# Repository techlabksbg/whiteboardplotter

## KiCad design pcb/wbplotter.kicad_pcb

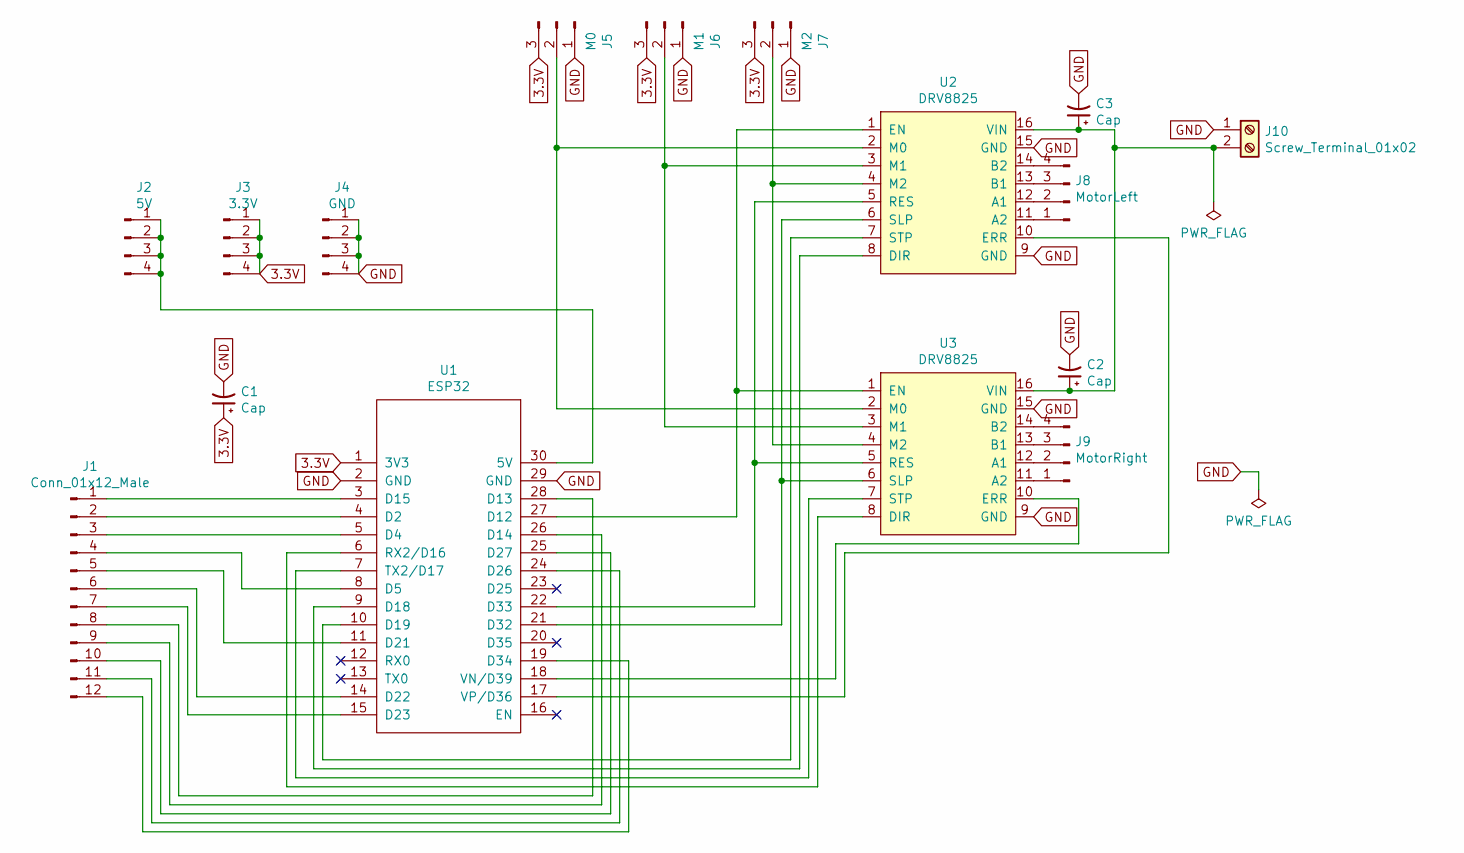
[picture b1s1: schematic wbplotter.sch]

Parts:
C1, C2, C3: Cap; CP_Radial_D6.3mm_P2.50mm
J1: Conn_01x12_Male; PinSocket_1x12_P2.54mm_Vertical
J2: 5V; PinSocket_1x04_P2.54mm_Vertical
J3: 3.3V; PinSocket_1x04_P2.54mm_Vertical
J4: GND; PinSocket_1x04_P2.54mm_Vertical
J5: M0; PinSocket_1x03_P2.54mm_Vertical
J6: M1; PinSocket_1x03_P2.54mm_Vertical
J7: M2; PinSocket_1x03_P2.54mm_Vertical
J8: MotorLeft; PinSocket_1x04_P2.54mm_Vertical
J9: MotorRight; PinSocket_1x04_P2.54mm_Vertical
J10: Screw_Terminal_01x02; TerminalBlock_Altech_AK300-2_P5.00mm
U1: ESP32; ESP32-Dev-Board
U2, U3: DRV8825

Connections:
3.3V: C1.1, J3.1, J3.2, J3.3, J3.4, J5.3, J6.3, J7.3, U1.1 (3V3)
GND: C1.2, C2.2, C3.2, J4.1, J4.2, J4.3, J4.4, J5.1, J6.1, J7.1, J10.1, U1.2 (GND), U1.29 (GND), U2.9 (GND), U2.15 (GND), U3.9 (GND), U3.15 (GND)
unnamed: C2.1, C3.1, J10.2, U2.16 (VIN), U3.16 (VIN)
unnamed: J1.1, U1.3 (D15)
unnamed: J1.2, U1.4 (D2)
unnamed: J1.3, U1.5 (D4)
unnamed: J1.4, U1.8 (D5)
unnamed: J1.5, U1.11 (D21)
unnamed: J1.6, U1.14 (D22)
unnamed: J1.7, U1.15 (D23)
unnamed: J1.8, U1.28 (D13)
unnamed: J1.9, U1.26 (D14)
unnamed: J1.10, U1.25 (D27)
unnamed: J1.11, U1.24 (D26)
unnamed: J1.12, U1.19 (D34)
unnamed: J2.1, J2.2, J2.3, J2.4, U1.30 (5V)
unnamed: J5.2, U2.2 (M0), U3.2 (M0)
unnamed: J6.2, U2.3 (M1), U3.3 (M1)
unnamed: J7.2, U2.4 (M2), U3.4 (M2)
unnamed: J8.1, U2.11 (A2)
unnamed: J8.2, U2.12 (A1)
unnamed: J8.3, U2.13 (B1)
unnamed: J8.4, U2.14 (B2)
unnamed: J9.1, U3.11 (A2)
unnamed: J9.2, U3.12 (A1)
unnamed: J9.3, U3.13 (B1)
unnamed: J9.4, U3.14 (B2)
unnamed: U1.6 (RX2/D16), U3.8 (DIR)
unnamed: U1.7 (TX2/D17), U3.7 (STP)
unnamed: U1.9 (D18), U2.8 (DIR)
unnamed: U1.10 (D19), U2.7 (STP)
unnamed: U1.17 (VP/D36), U2.10 (ERR)
unnamed: U1.18 (VN/D39), U3.10 (ERR)
unnamed: U1.21 (D32), U2.6 (SLP), U3.6 (SLP)
unnamed: U1.22 (D33), U2.5 (RES), U3.5 (RES)
unnamed: U1.27 (D12), U2.1 (EN), U3.1 (EN)

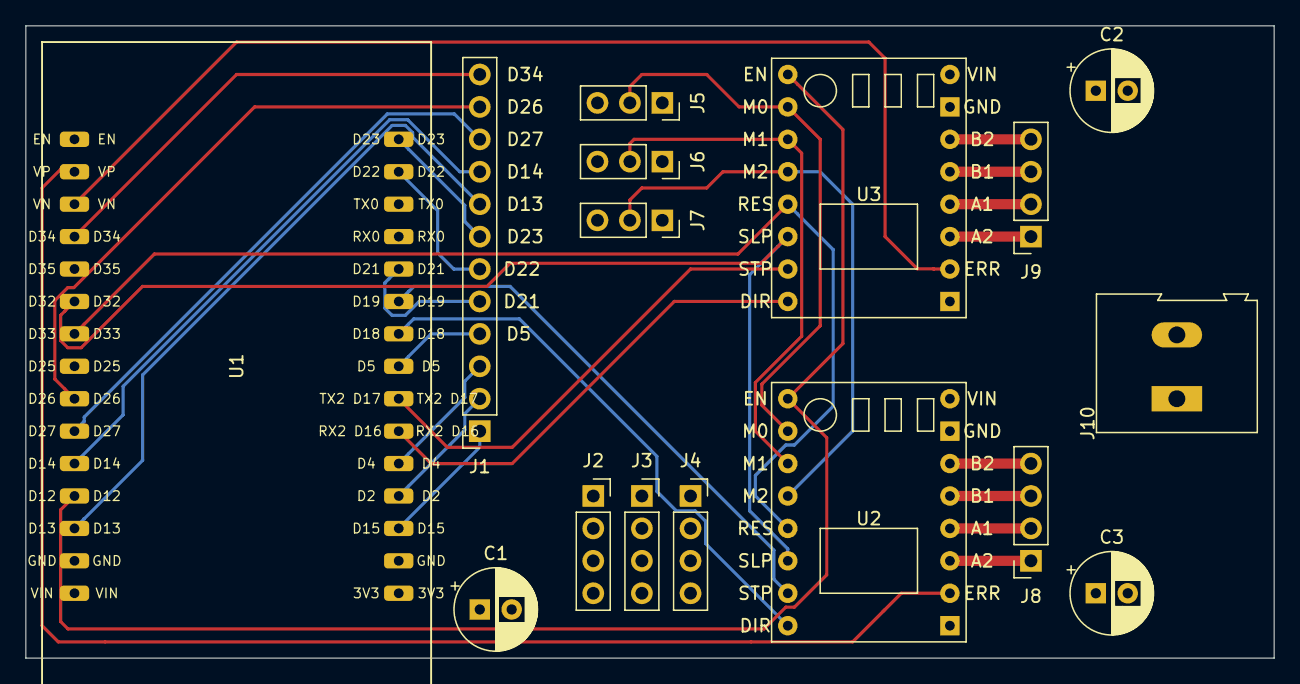
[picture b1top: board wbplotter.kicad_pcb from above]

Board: 2 copper layers, 97.8 x 49.5 mm, 16 parts (0 on the bottom side), 36 nets.

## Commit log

2021-06-04 first
